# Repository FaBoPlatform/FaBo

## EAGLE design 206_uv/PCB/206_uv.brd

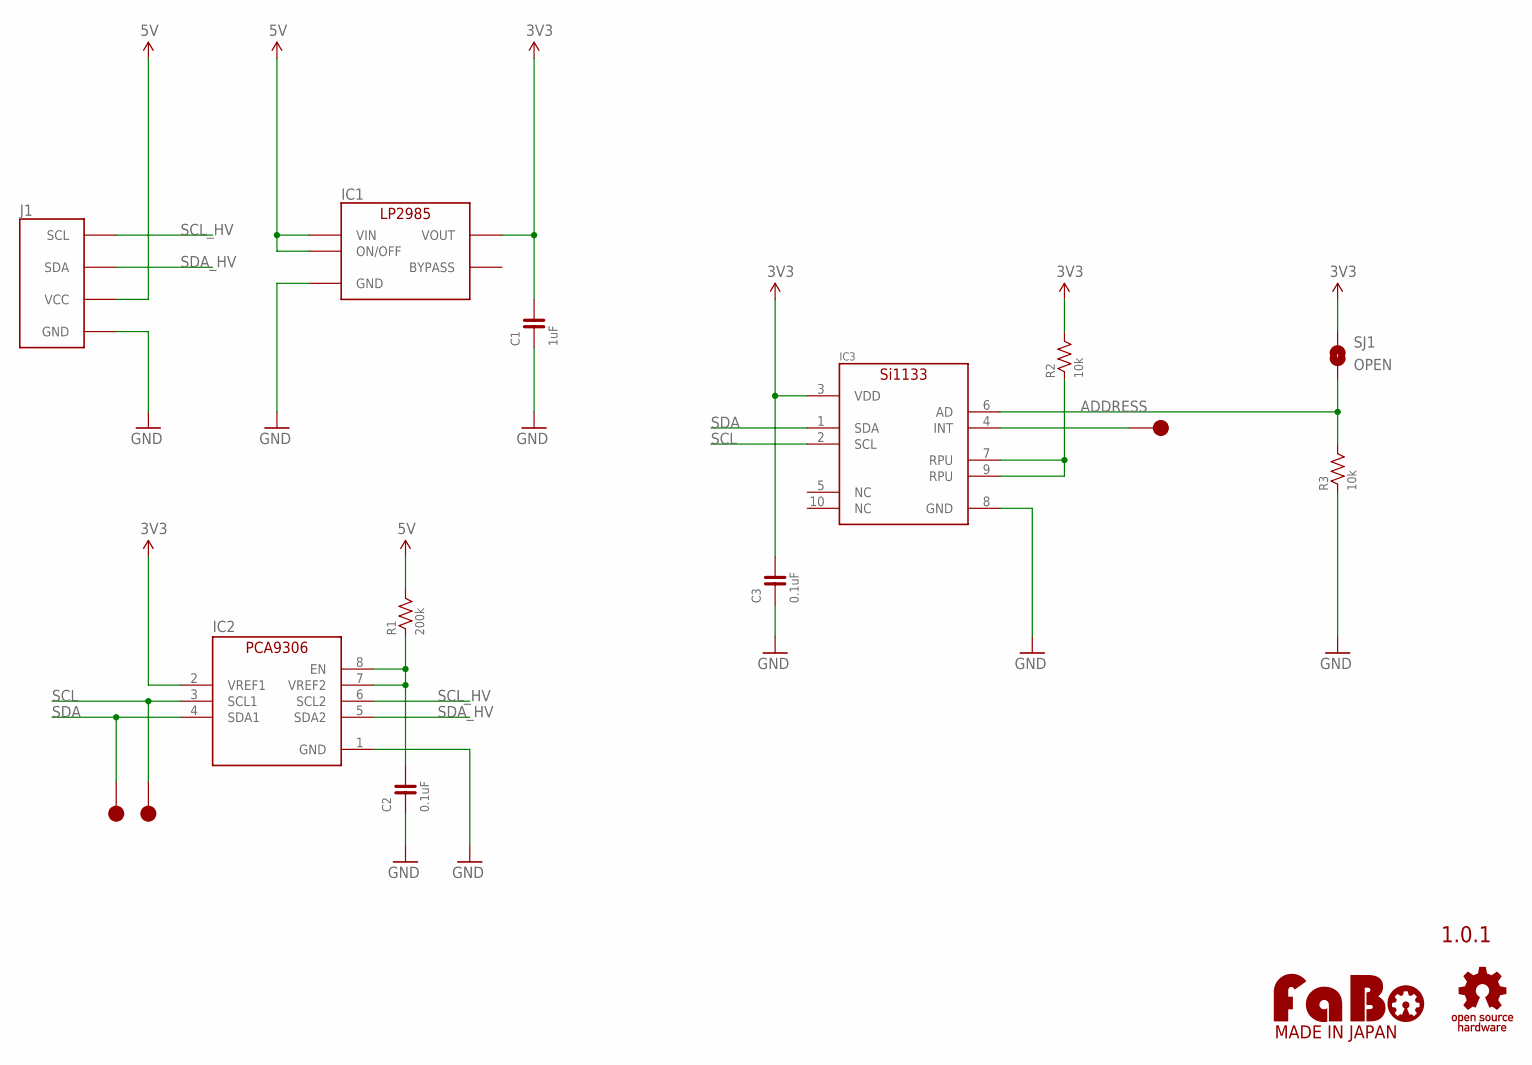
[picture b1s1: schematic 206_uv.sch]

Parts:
C1: 1uF; 0603
C2, C3: 0.1uF; 0603
IC1: LP2985-33DBV; SOT-23-5
IC2: PCA9306DQER; X2SON
IC3: SILICONLABS-SI1133
J1: FABO_BRICK_I2C
R1: 200k; 0603
R2, R3: 10k; 0603
SJ1: OPEN; SMD-JUMPER-2-OPEN
TP1, TP2, TP3: TP-10
U$2: LOGO_FABO-M; LOGO_FABO_MS
U$3: LOGO_OSHW-M_BOTTOM; LOGO_OSHW_M_BOTTOM

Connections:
3V3: C1.2, C3.2, IC1.5 (VOUT), IC2.2 (VREF1), IC3.3 (VDD), R2.2, SJ1.1
5V: IC1.1 (VIN), IC1.3 (ON/OFF), J1.VCC, R1.2
ADDRESS: IC3.6 (AD), R3.2, SJ1.2
GND: C1.1, C2.1, C3.1, IC1.2 (GND), IC2.1 (GND), IC3.8 (GND), J1.GND, R3.1
unnamed: C2.2, IC2.7 (VREF2), IC2.8 (EN), R1.1
unnamed: IC3.7 (RPU), IC3.9 (RPU), R2.1
unnamed: IC3.4 (INT), TP3.1
SCL: IC2.3 (SCL1), IC3.2 (SCL), TP2.1
SCL_HV: IC2.6 (SCL2), J1.SCL
SDA: IC2.4 (SDA1), IC3.1 (SDA), TP1.1
SDA_HV: IC2.5 (SDA2), J1.SDA

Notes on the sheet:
1.0.1

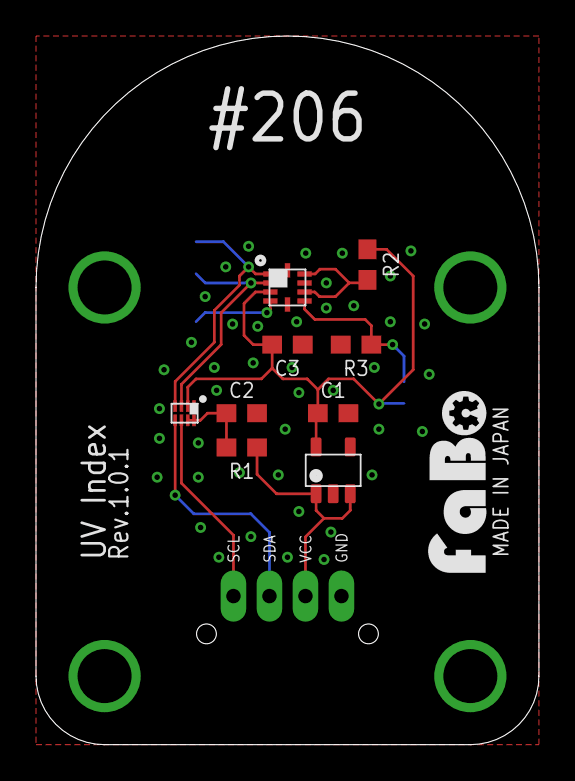
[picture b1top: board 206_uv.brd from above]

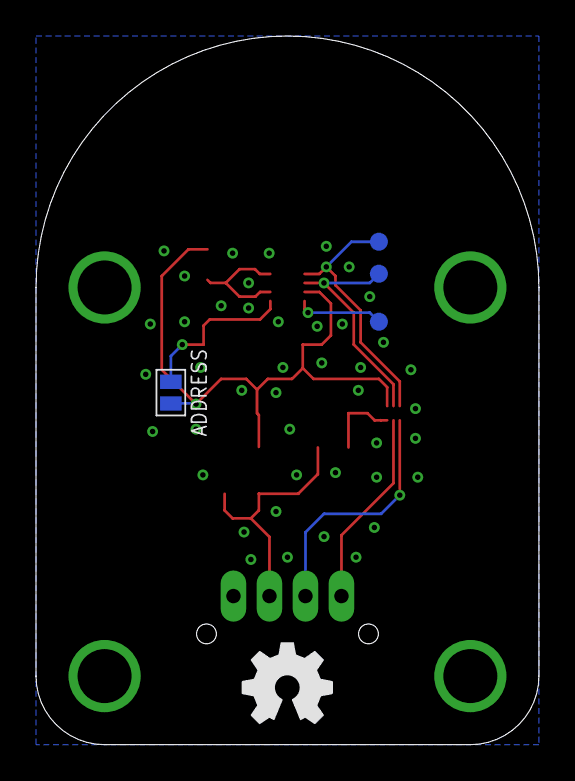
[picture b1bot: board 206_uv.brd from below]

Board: 2 copper layers, 27.9 x 39.4 mm, 16 parts (4 on the bottom side), 11 nets.

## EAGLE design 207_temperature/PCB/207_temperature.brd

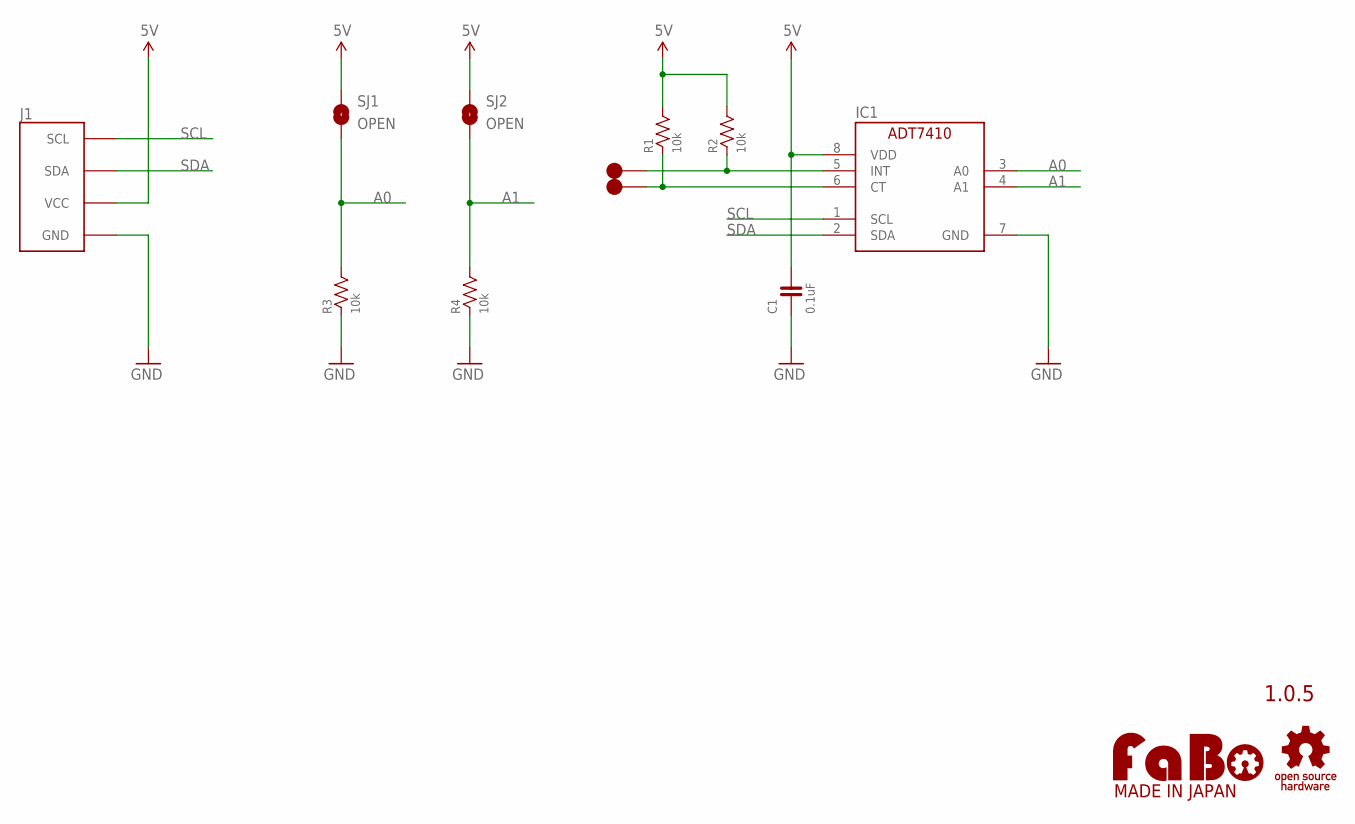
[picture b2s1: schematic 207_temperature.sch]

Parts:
C1: 0.1uF; 0603
IC1: AD-ADT7410; ANALOGDEVICES-ADT7410
J1: FABO_BRICK_I2C
R1, R2, R3, R4: 10k; 0603
SJ1, SJ2: OPEN; SMD-JUMPER-2-OPEN
TP1, TP2: TP-15
U$1: LOGO_OSHW-M_BOTTOM; LOGO_OSHW_M_BOTTOM
U$3: LOGO_FABO-M; LOGO_FABO_MS

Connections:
5V: C1.2, IC1.8 (VDD), J1.VCC, R1.2, R2.2, SJ1.1, SJ2.1
A0: IC1.3 (A0), R3.2, SJ1.2
A1: IC1.4 (A1), R4.2, SJ2.2
GND: C1.1, IC1.7 (GND), J1.GND, R3.1, R4.1
unnamed: IC1.6 (CT), R1.1, TP2.1
unnamed: IC1.5 (INT), R2.1, TP1.1
SCL: IC1.1 (SCL), J1.SCL
SDA: IC1.2 (SDA), J1.SDA

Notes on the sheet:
1.0.5

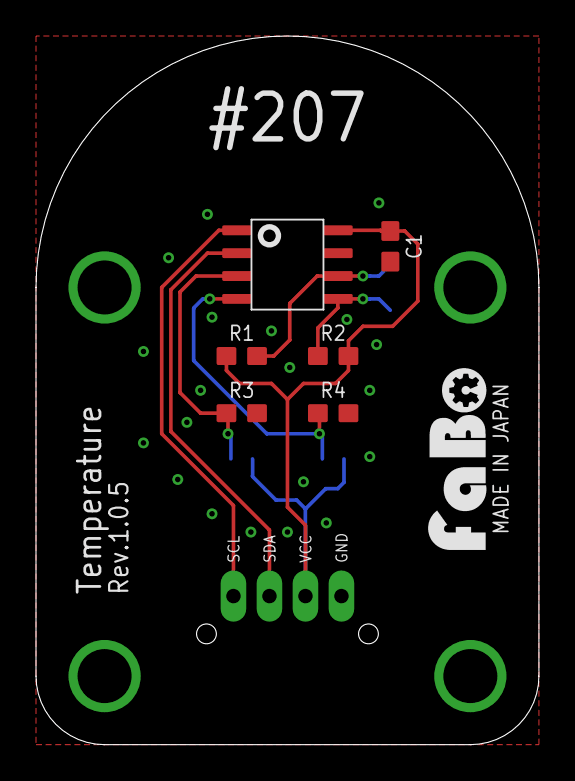
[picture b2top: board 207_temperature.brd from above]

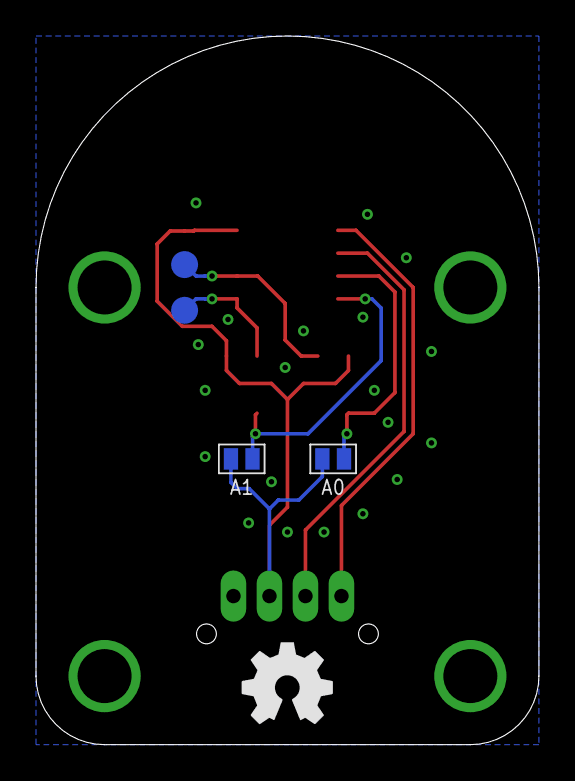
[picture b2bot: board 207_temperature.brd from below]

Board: 2 copper layers, 27.9 x 39.4 mm, 13 parts (4 on the bottom side), 8 nets.

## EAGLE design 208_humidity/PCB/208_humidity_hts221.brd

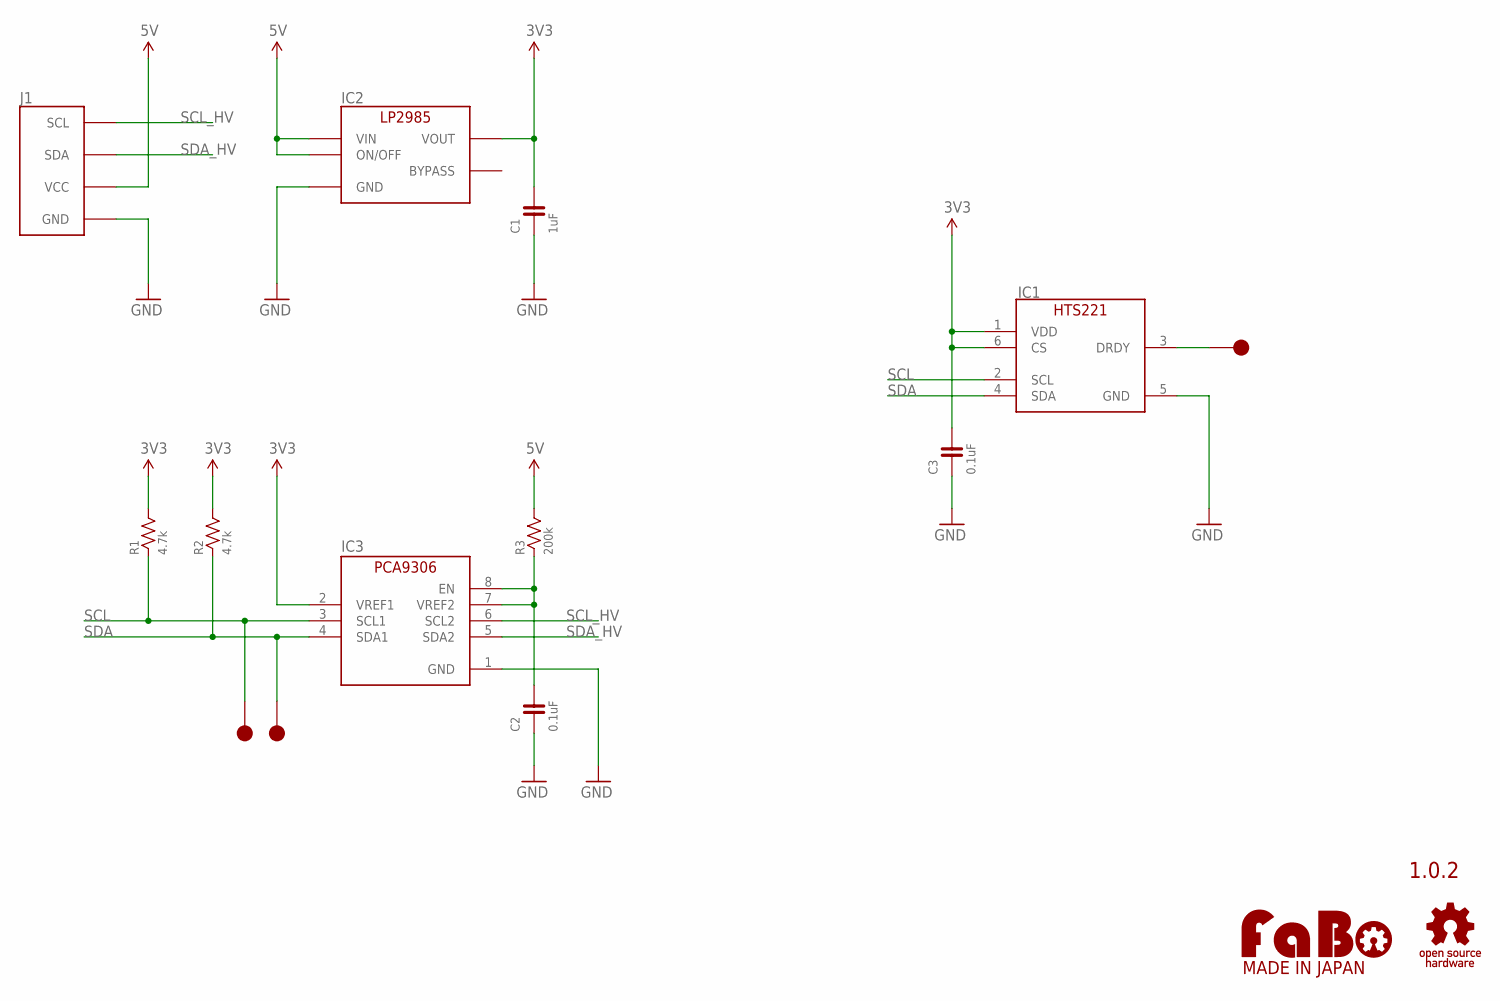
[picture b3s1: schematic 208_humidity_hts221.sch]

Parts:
C1: 1uF; 0603
C2, C3: 0.1uF; 0603
IC1: ST-HTS221
IC2: LP2985-33DBV; SOT-23-5
IC3: PCA9306GM; XQFN8
J1: FABO_BRICK_I2C
R1, R2: 4.7k; 0603
R3: 200k; 0603
TP1, TP2, TP3: TP-15
U$2: LOGO_FABO-M; LOGO_FABO_MS
U$3: LOGO_OSHW-M_BOTTOM; LOGO_OSHW_M_BOTTOM

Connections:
3V3: C1.2, C3.2, IC1.1 (VDD), IC1.6 (CS), IC2.5 (VOUT), IC3.2 (VREF1), R1.2, R2.2
5V: IC2.1 (VIN), IC2.3 (ON/OFF), J1.VCC, R3.2
GND: C1.1, C2.1, C3.1, IC1.5 (GND), IC2.2 (GND), IC3.1 (GND), J1.GND
unnamed: C2.2, IC3.7 (VREF2), IC3.8 (EN), R3.1
unnamed: IC1.3 (DRDY), TP3.1
SCL: IC1.2 (SCL), IC3.3 (SCL1), R1.1, TP2.1
SCL_HV: IC3.6 (SCL2), J1.SCL
SDA: IC1.4 (SDA), IC3.4 (SDA1), R2.1, TP1.1
SDA_HV: IC3.5 (SDA2), J1.SDA

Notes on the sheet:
1.0.2

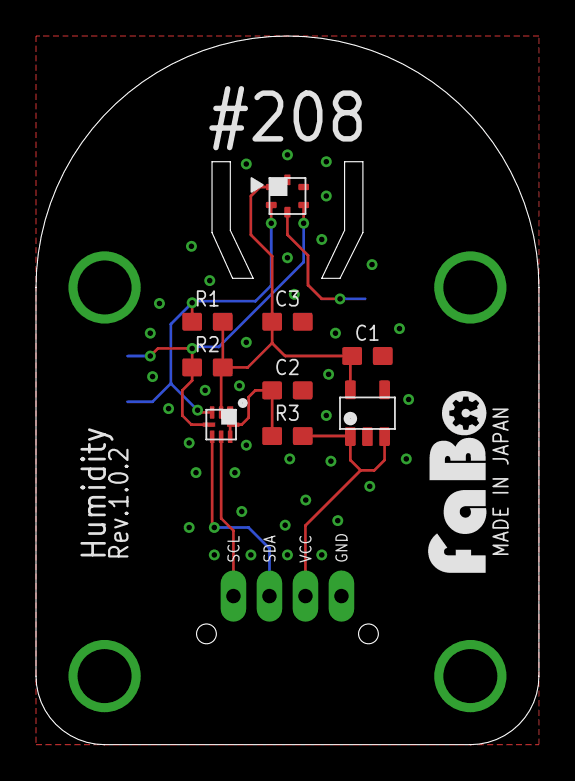
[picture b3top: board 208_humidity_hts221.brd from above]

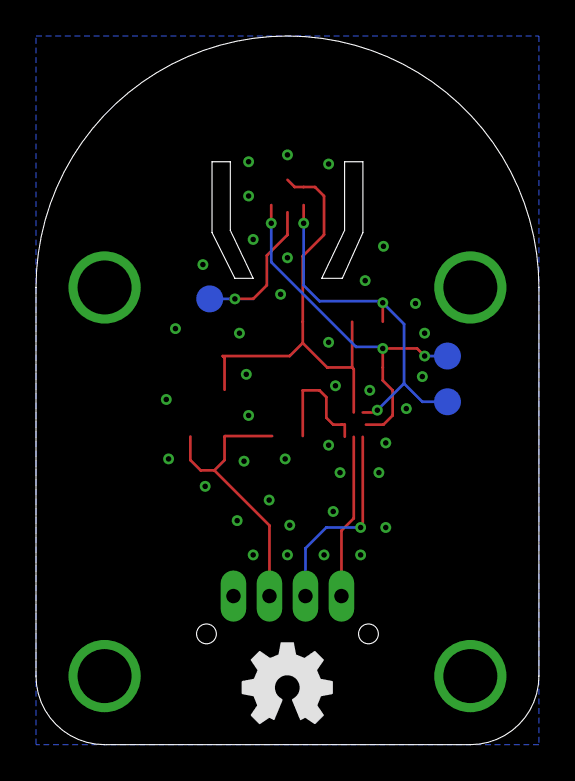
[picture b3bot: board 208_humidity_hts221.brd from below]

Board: 2 copper layers, 27.9 x 39.4 mm, 15 parts (3 on the bottom side), 9 nets.

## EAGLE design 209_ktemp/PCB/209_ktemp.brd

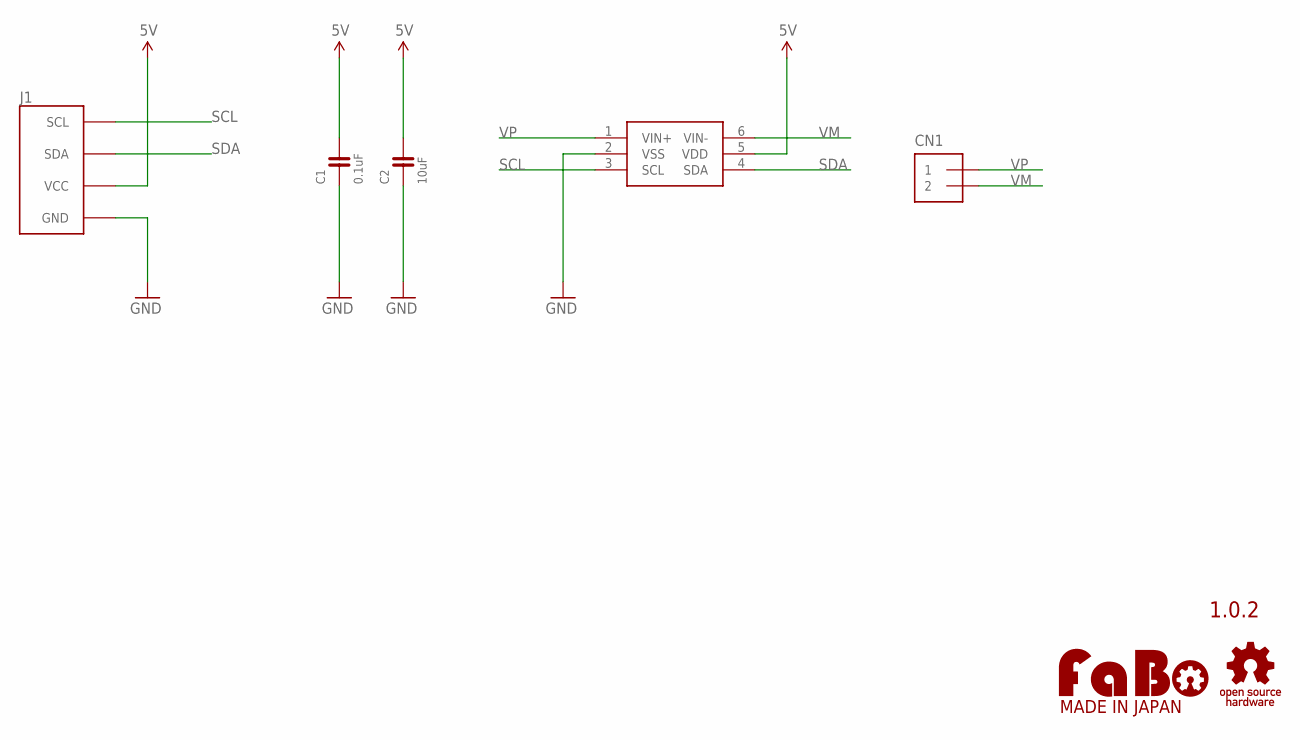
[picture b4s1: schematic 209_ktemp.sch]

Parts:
C1: 0.1uF; 0603
C2: 10uF; 0603
CN1: PIN_HEADER_1X2; PIN_1X2_LONG
J1: FABO_BRICK_I2C
U$2: MICROCHIP-MCP3421
U$3: LOGO_OSHW-M_BOTTOM; LOGO_OSHW_M_BOTTOM
U$4: LOGO_FABO-M; LOGO_FABO_MS

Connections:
5V: C1.2, C2.2, J1.VCC, U$2.5 (VDD)
GND: C1.1, C2.1, J1.GND, U$2.2 (VSS)
SCL: J1.SCL, U$2.3 (SCL)
SDA: J1.SDA, U$2.4 (SDA)
VM: CN1.2, U$2.6 (VIN-)
VP: CN1.1, U$2.1 (VIN+)

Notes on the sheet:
1.0.2

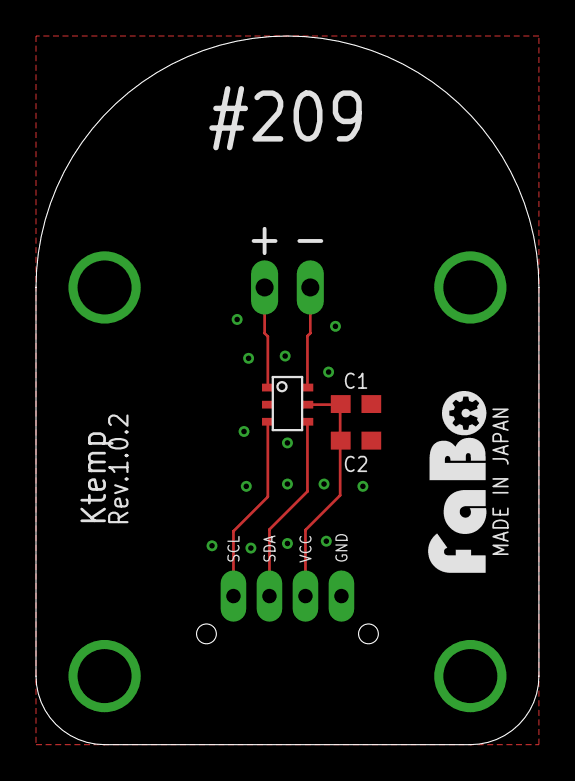
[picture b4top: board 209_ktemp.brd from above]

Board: 2 copper layers, 27.9 x 39.4 mm, 7 parts (0 on the bottom side), 6 nets.

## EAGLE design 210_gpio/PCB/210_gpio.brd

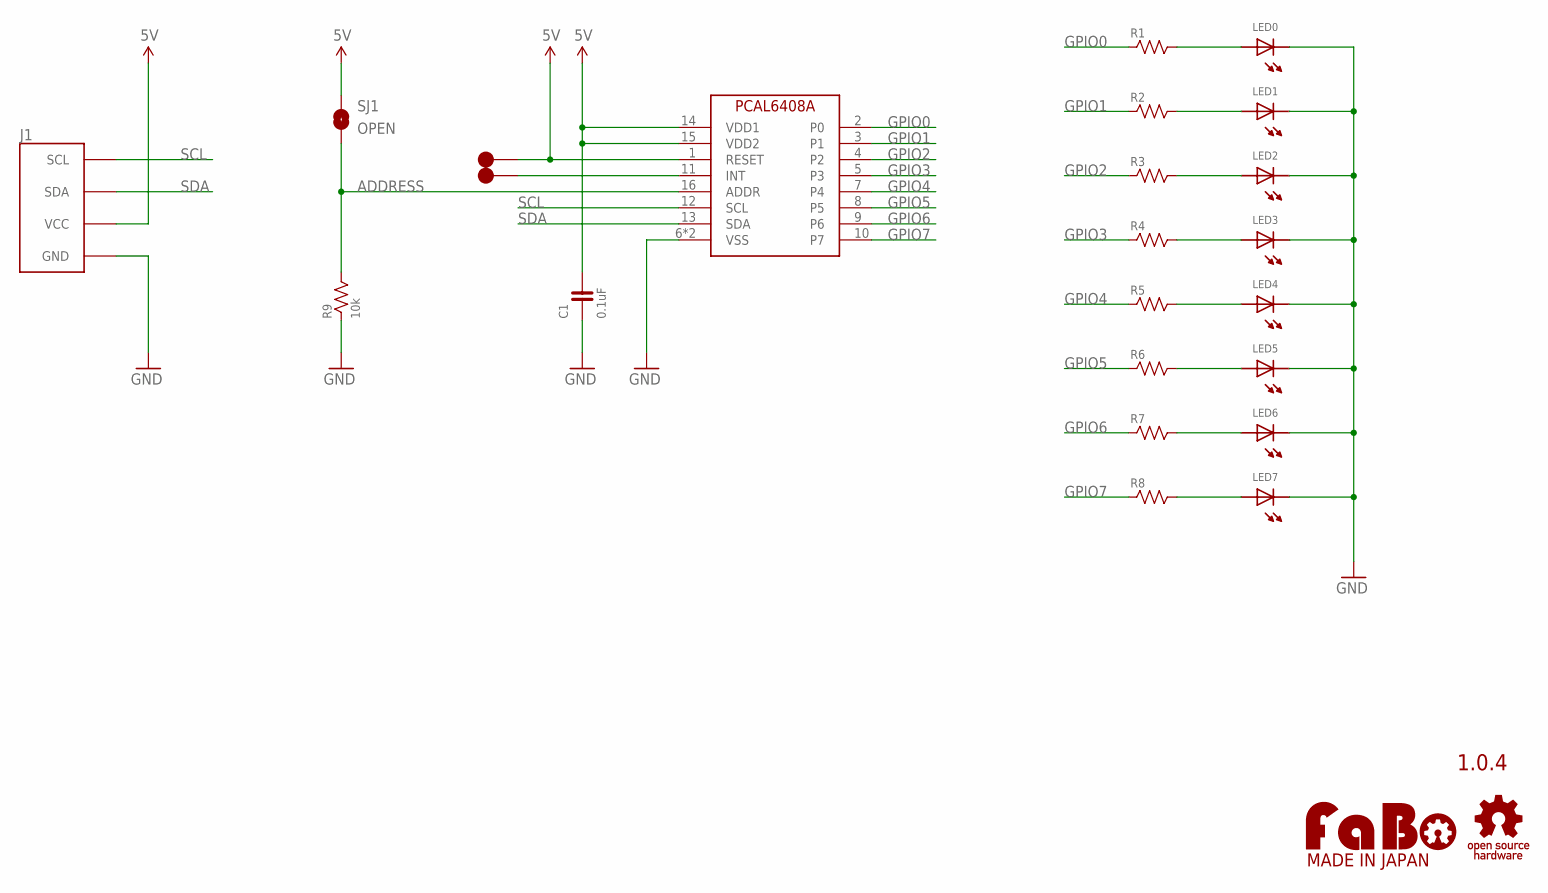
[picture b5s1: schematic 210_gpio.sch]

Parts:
C1: 0.1uF; 0603
IC1: NX-PCAL6408A; NXP-PCAL6408A
J1: FABO_BRICK_I2C
LED0, LED1, LED2, LED3, LED4, LED5, LED6, LED7: LED-0603-NARROW; 0603-NARROW
R1, R2, R3, R4, R5, R6, R7, R8: RESISTOR-0603-NARROW; 0603-NARROW
R9: 10k; 0603-NARROW
SJ1: OPEN; SMD-JUMPER-2-OPEN
TP1, TP2: TP-10
U$2: LOGO_OSHW-M_BOTTOM; LOGO_OSHW_M_BOTTOM
U$4: LOGO_FABO-M; LOGO_FABO_MS

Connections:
ADDRESS: IC1.16 (ADDR), R9.2, SJ1.2
GND: C1.1, IC1.6 (VSS), IC1.17 (VSS), J1.GND, LED0.CATHODE, LED1.CATHODE, LED2.CATHODE, LED3.CATHODE, LED4.CATHODE, LED5.CATHODE, LED6.CATHODE, LED7.CATHODE, R9.1
GPIO0: IC1.2 (P0), R1.1
GPIO1: IC1.3 (P1), R2.1
GPIO2: IC1.4 (P2), R3.1
GPIO3: IC1.5 (P3), R4.1
GPIO4: IC1.7 (P4), R5.1
GPIO5: IC1.8 (P5), R6.1
GPIO6: IC1.9 (P6), R7.1
GPIO7: IC1.10 (P7), R8.1
unnamed: LED0.ANODE, R1.2
unnamed: LED1.ANODE, R2.2
unnamed: LED2.ANODE, R3.2
unnamed: LED3.ANODE, R4.2
unnamed: LED4.ANODE, R5.2
unnamed: LED5.ANODE, R6.2
unnamed: LED6.ANODE, R7.2
unnamed: LED7.ANODE, R8.2
SCL: IC1.12 (SCL), J1.SCL
SDA: IC1.13 (SDA), J1.SDA

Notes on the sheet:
1.0.4

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
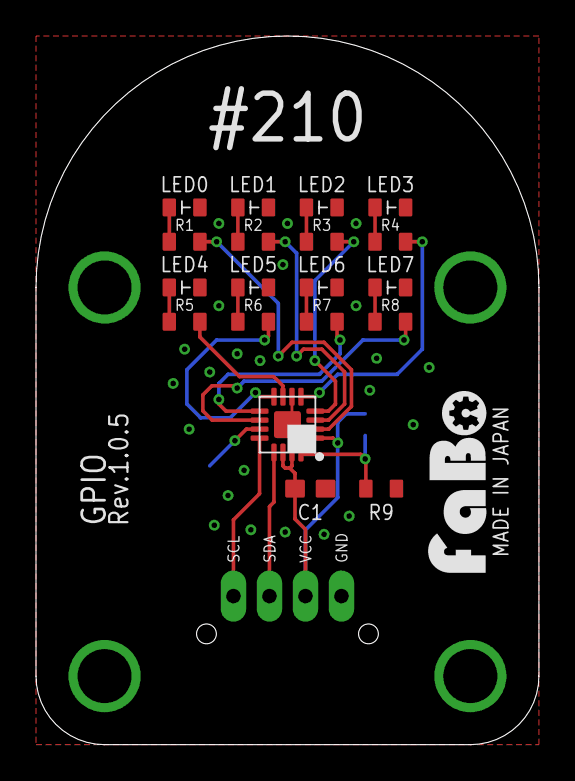
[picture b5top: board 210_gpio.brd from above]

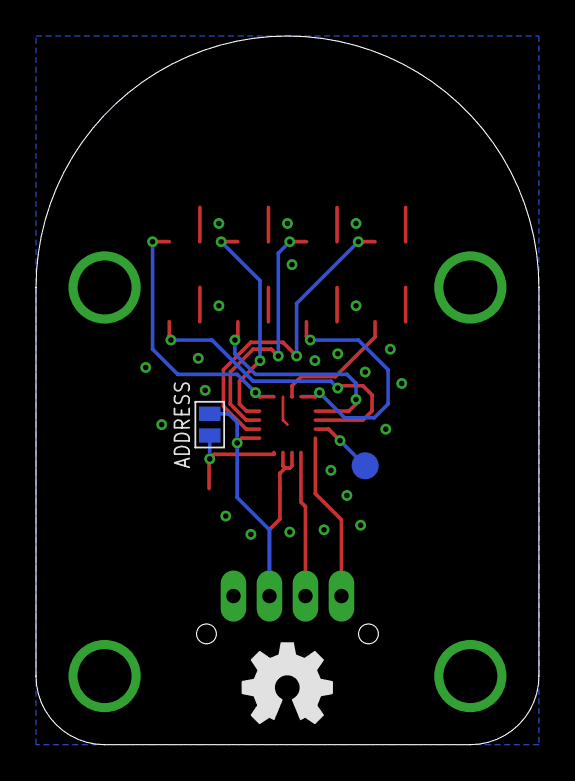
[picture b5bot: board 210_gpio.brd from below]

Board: 2 copper layers, 27.9 x 39.4 mm, 24 parts (2 on the bottom side), 22 nets.

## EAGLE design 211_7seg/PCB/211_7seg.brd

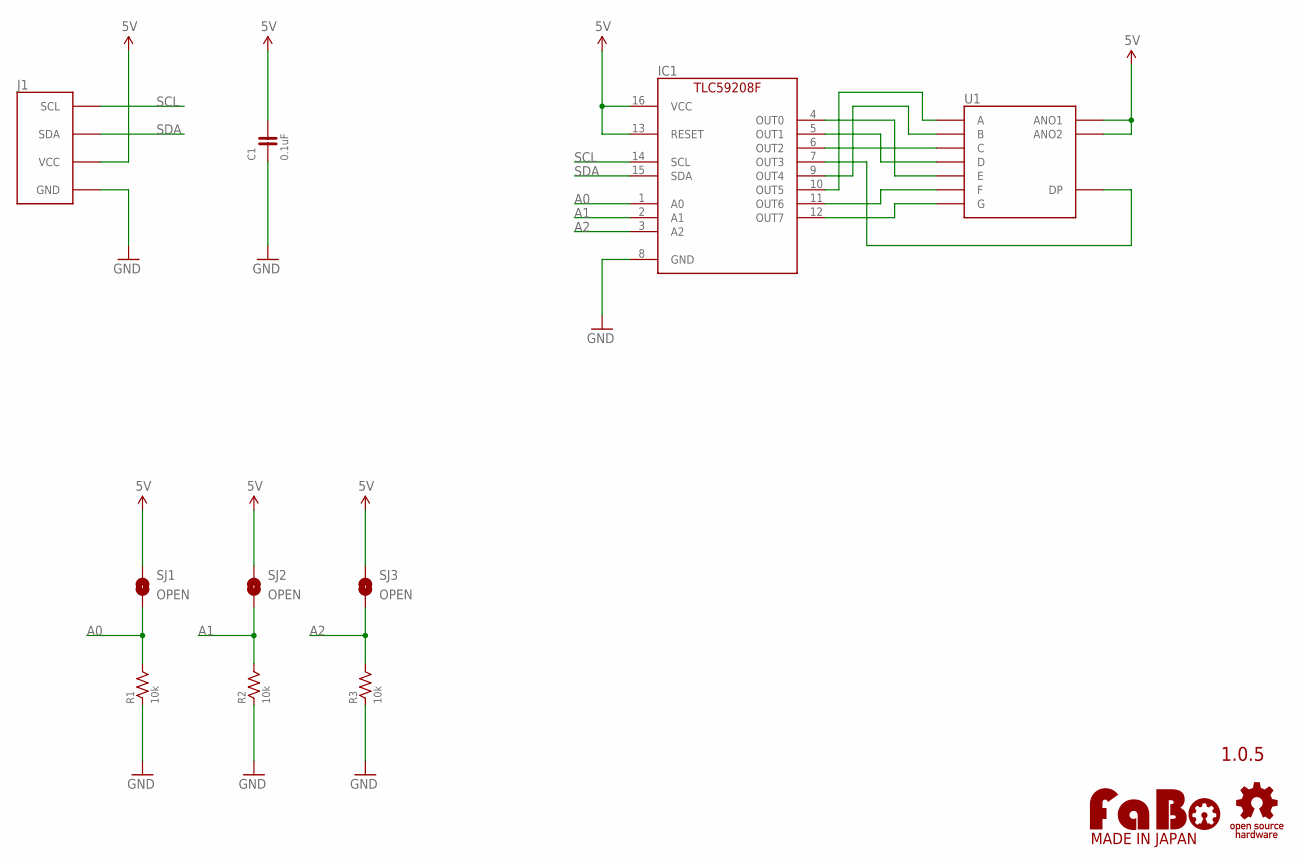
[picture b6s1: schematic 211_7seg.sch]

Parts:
C1: 0.1uF; 0603
IC1: TLC59208FIPWR; TSSOP16
J1: FABO_BRICK_I2C
R1, R2, R3: 10k; 0603
SJ1, SJ2, SJ3: OPEN; SMD-JUMPER-2-OPEN
U1: 7SEG_ANO; A-551SRD
U$2: LOGO_OSHW-M_BOTTOM; LOGO_OSHW_M_BOTTOM
U$4: LOGO_FABO-M; LOGO_FABO_MS

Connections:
5V: C1.2, IC1.13 (RESET), IC1.16 (VCC), J1.VCC, SJ1.1, SJ2.1, SJ3.1, U1.ANO1, U1.ANO2
A0: IC1.1 (A0), R1.2, SJ1.2
A1: IC1.2 (A1), R2.2, SJ2.2
A2: IC1.3 (A2), R3.2, SJ3.2
GND: C1.1, IC1.8 (GND), J1.GND, R1.1, R2.1, R3.1
unnamed: IC1.4 (OUT0), U1.E
unnamed: IC1.5 (OUT1), U1.D
unnamed: IC1.6 (OUT2), U1.C
unnamed: IC1.7 (OUT3), U1.DP
unnamed: IC1.9 (OUT4), U1.B
unnamed: IC1.10 (OUT5), U1.A
unnamed: IC1.11 (OUT6), U1.F
unnamed: IC1.12 (OUT7), U1.G
SCL: IC1.14 (SCL), J1.SCL
SDA: IC1.15 (SDA), J1.SDA

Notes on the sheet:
1.0.5

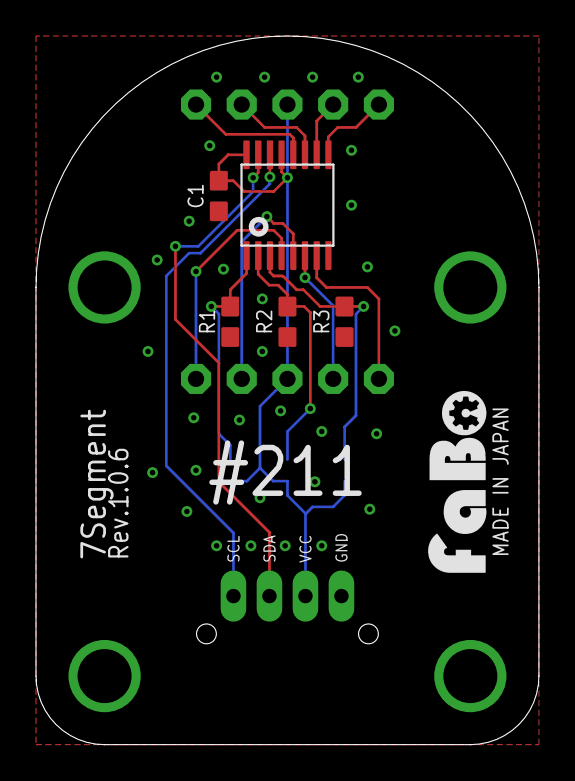
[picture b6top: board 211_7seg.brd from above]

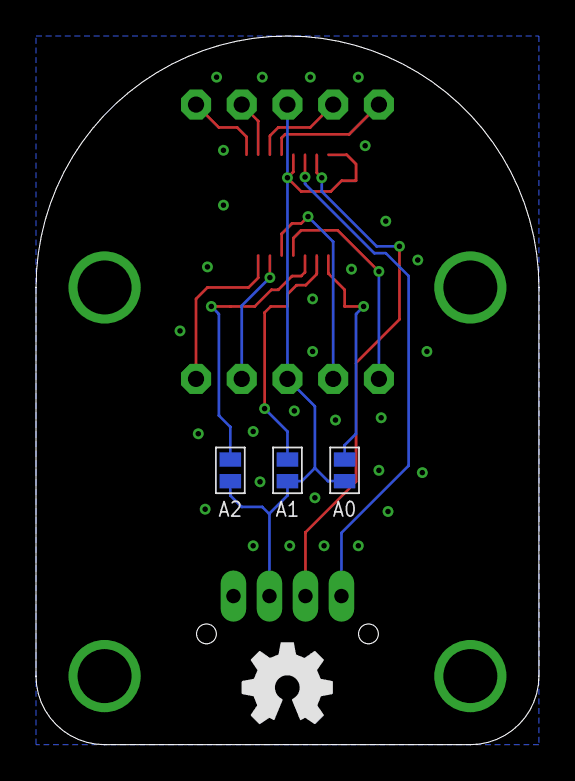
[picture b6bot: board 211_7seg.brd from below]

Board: 2 copper layers, 27.9 x 39.4 mm, 12 parts (3 on the bottom side), 15 nets.

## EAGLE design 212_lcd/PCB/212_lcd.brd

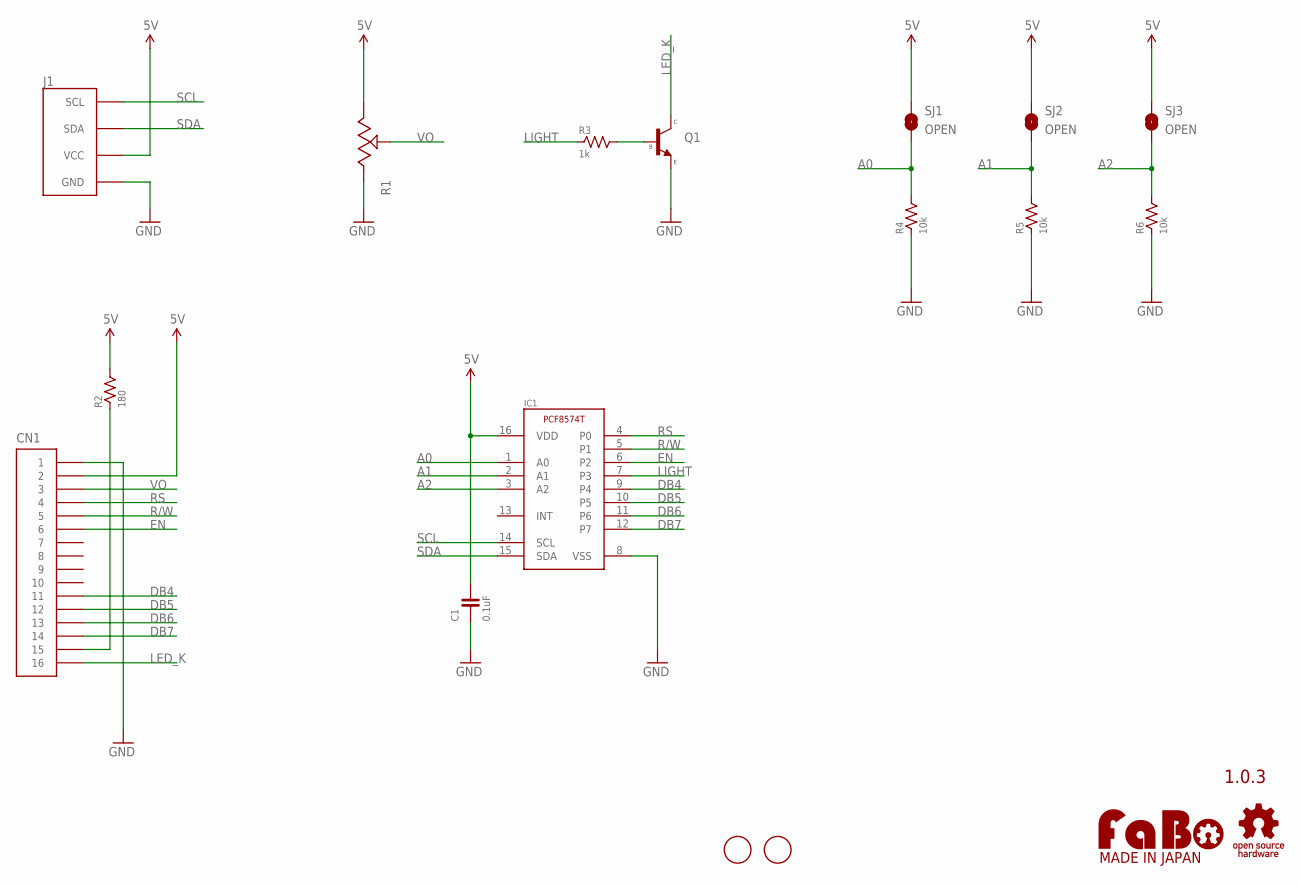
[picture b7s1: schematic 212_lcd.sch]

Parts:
C1: 0.1uF; 0603
CN1: PIN_HEADER_1X16-LONG; PIN_1X16_LONG
IC1: PCF8574T; SO16
J1: FABO_BRICK_I2C-S04B-PASK-2_LONG; FABO_BRICK_I2C_S04B-PASK-2_LONG
Q1: NPN-SMD; SOT23
R1: RESISTOR_VARIABLE-SMD; TC33X
R2: 180; 0603
R3: 1k; 0603
R4, R5, R6: 10k; 0603
SJ1, SJ2, SJ3: OPEN; SMD-JUMPER-2-OPEN
U$2: LOGO_OSHW-M_BOTTOM; LOGO_OSHW_M_BOTTOM
U$3: LOGO_FABO-M; LOGO_FABO_MS
U$4, U$5: SCREW-PAD-3MM; SCREWPAD_3MM

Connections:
5V: C1.2, CN1.2, IC1.16 (VDD), J1.VCC, R1.1, R2.2, SJ1.1, SJ2.1, SJ3.1
A0: IC1.1 (A0), R4.2, SJ1.2
A1: IC1.2 (A1), R5.2, SJ2.2
A2: IC1.3 (A2), R6.2, SJ3.2
BASE: Q1.1 (B), R3.2
DB4: CN1.11, IC1.9 (P4)
DB5: CN1.12, IC1.10 (P5)
DB6: CN1.13, IC1.11 (P6)
DB7: CN1.14, IC1.12 (P7)
EN: CN1.6, IC1.6 (P2)
GND: C1.1, CN1.1, IC1.8 (VSS), J1.GND, Q1.2 (E), R1.3, R4.1, R5.1, R6.1
LED_A: CN1.15, R2.1
LED_K: CN1.16, Q1.3 (C)
LIGHT: IC1.7 (P3), R3.1
R/W: CN1.5, IC1.5 (P1)
RS: CN1.4, IC1.4 (P0)
SCL: IC1.14 (SCL), J1.SCL
SDA: IC1.15 (SDA), J1.SDA
VO: CN1.3, R1.2

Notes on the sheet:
1.0.3

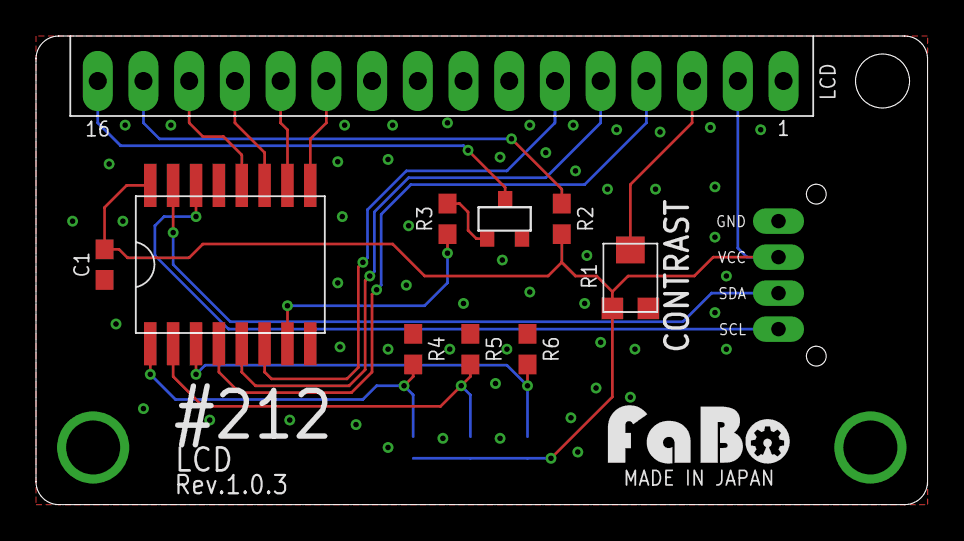
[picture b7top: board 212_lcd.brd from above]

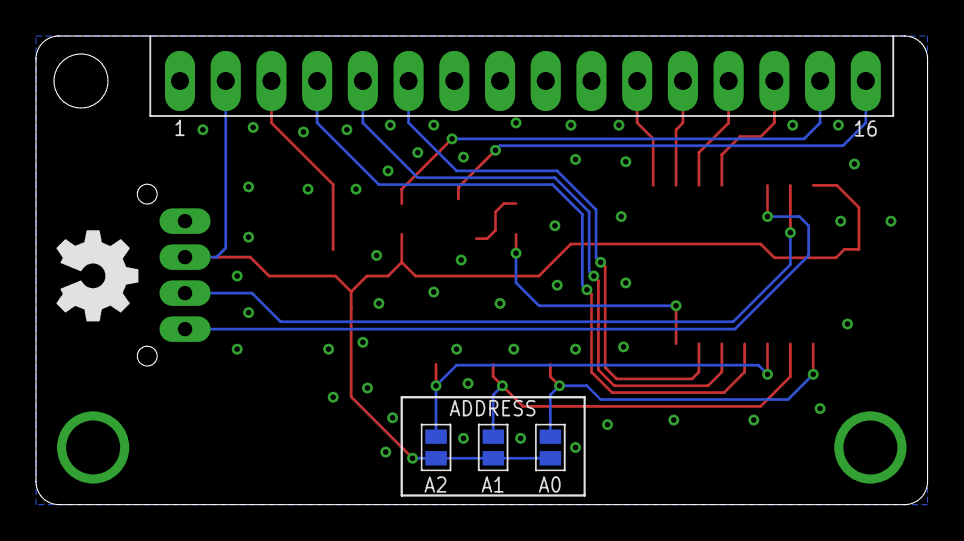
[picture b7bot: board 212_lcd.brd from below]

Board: 2 copper layers, 49.5 x 26.0 mm, 18 parts (3 on the bottom side), 19 nets.

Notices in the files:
parts and their libraries:
FaBo-Template: Released under the Creative Commons Attribution-ShareAlike 4.0 License
https://creativecommons.org/licenses/by-sa/4.0
GClue: Released under the Creative Commons
